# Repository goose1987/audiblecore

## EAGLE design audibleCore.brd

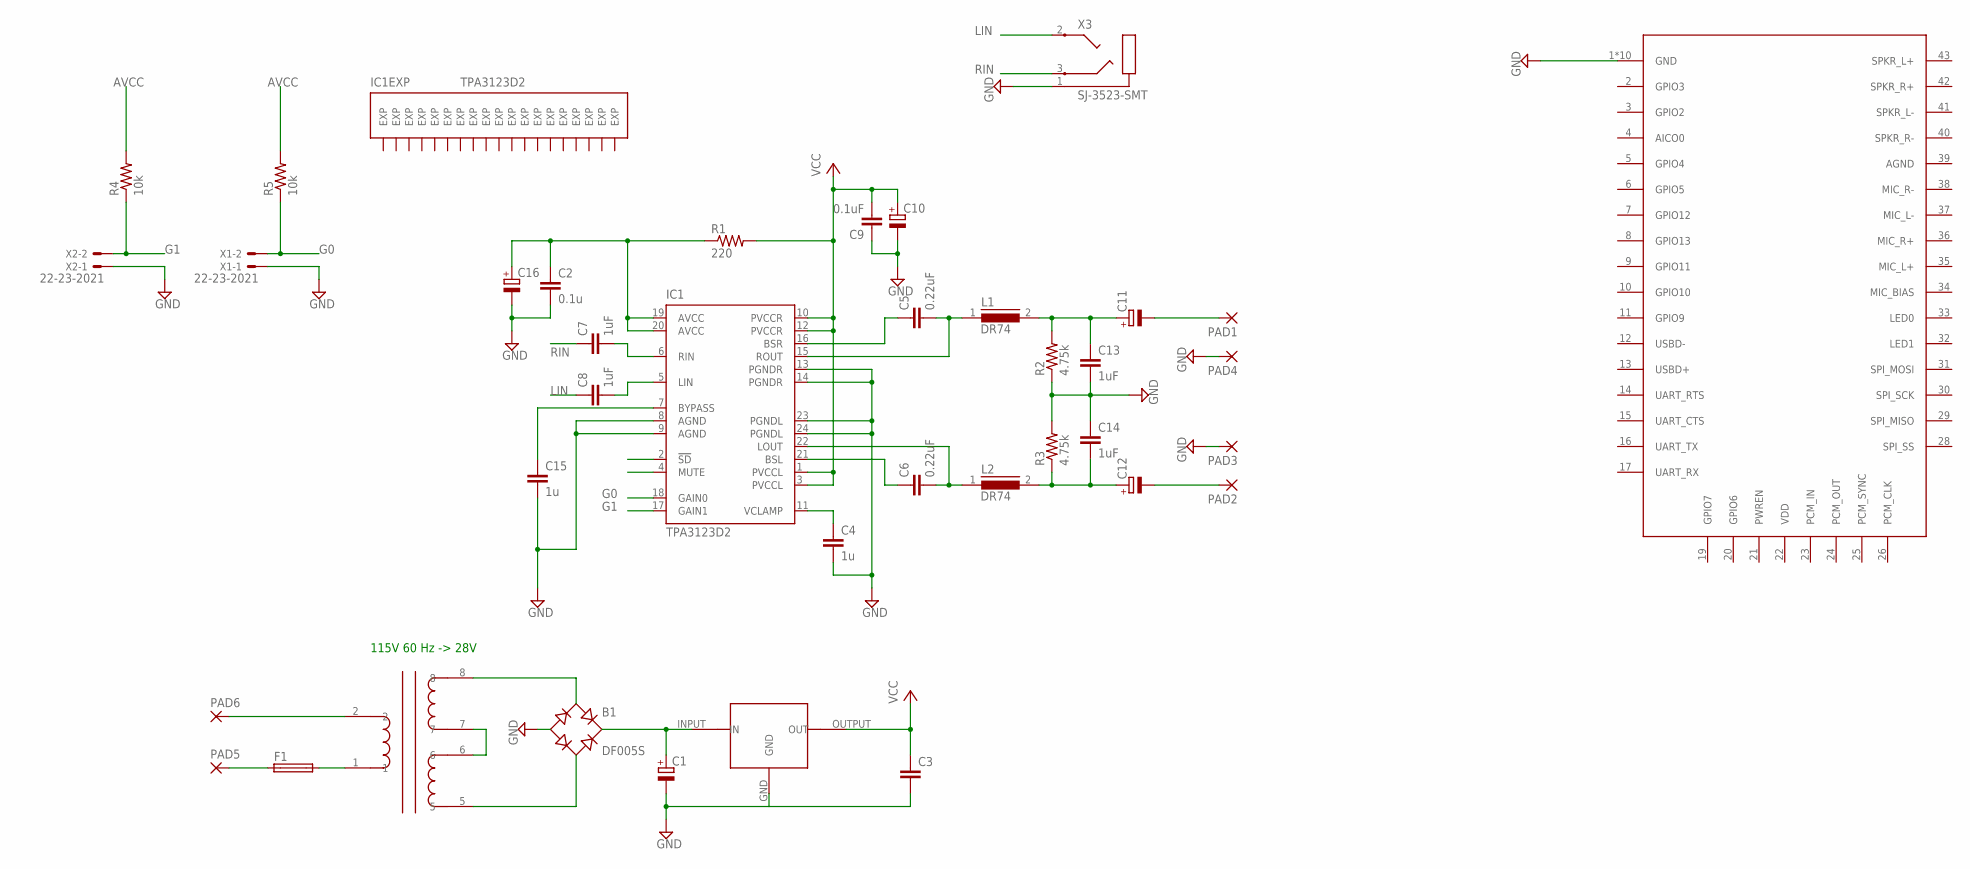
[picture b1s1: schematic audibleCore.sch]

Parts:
B1: DF005S; DFS
C1, C10, C11, C12, C16: CPOL-EUG; PANASONIC_G
C2: 0.1u; C1206
C3: C-EUC1206; C1206
C4, C15: 1u; C1206
C5, C6: 0.22uF; C1206
C7, C8, C13, C14: 1uF; C1206
C9: 0.1uF; C1206
F1: GSH15
IC1: TPA3123D2; PWP-TSSOP24
L1, L2: DR74
PAD1, PAD2, PAD3, PAD4, PAD5, PAD6: SMD5; SMD2,54-5,08
R1: 220; R1206
R2, R3: 4.75k; R1206
R4, R5: 10k; R1206
U$1: ST-7-24; ST-7
U$2: L78XX; D2PAK
U$3: RN-52
X1, X2: 22-23-2021
X3: SJ-3523-SMT

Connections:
AVCC: C2.1, C16.+, IC1.19 (AVCC), IC1.20 (AVCC), R1.1, R4.2, R5.2
G0: IC1.18 (GAIN0), R5.1, X1.2
G1: IC1.17 (GAIN1), R4.1, X2.2
GND: B1.-, C1.-, C2.2, C3.2, C4.2, C9.1, C10.-, C13.2, C14.1, C15.2, C16.-, IC1.8 (AGND), IC1.9 (AGND), IC1.13 (PGNDR), IC1.14 (PGNDR), IC1.23 (PGNDL), IC1.24 (PGNDL), PAD3.1, PAD4.1, R2.1, R3.2, U$2.GND, U$3.1 (GND), U$3.18 (GND), U$3.27 (GND), U$3.44 (GND), U$3.45 (GND), U$3.46 (GND), U$3.47 (GND), U$3.48 (GND), U$3.49 (GND), U$3.50 (GND), X1.1, X2.1, X3.1 (EARTH)
LIN: C8.1, X3.2 (TIP)
unnamed: U$1.6, U$1.7
unnamed: B1.AC1, U$1.8
unnamed: B1.AC2, U$1.5
unnamed: B1.+, C1.+, U$2.INPUT (IN)
unnamed: C12.-, PAD2.1
unnamed: C4.1, IC1.11 (VCLAMP)
unnamed: C5.1, IC1.16 (BSR)
unnamed: C6.1, IC1.21 (BSL)
unnamed: C6.2, IC1.22 (LOUT), L2.1
unnamed: C5.2, IC1.15 (ROUT), L1.1
unnamed: C15.1, IC1.7 (BYPASS)
unnamed: C7.2, IC1.6 (RIN)
unnamed: C8.2, IC1.5 (LIN)
unnamed: C11.+, C13.1, L1.2, R2.2
unnamed: C12.+, C14.2, L2.2, R3.1
unnamed: C11.-, PAD1.1
unnamed: PAD6.1, U$1.2
unnamed: F1.2, U$1.1
unnamed: F1.1, PAD5.1
RIN: C7.1, X3.3 (RING)
VCC: C3.1, C9.2, C10.+, IC1.1 (PVCCL), IC1.3 (PVCCL), IC1.10 (PVCCR), IC1.12 (PVCCR), R1.2, U$2.OUTPUT (OUT)

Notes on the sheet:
115V 60 Hz -> 28V

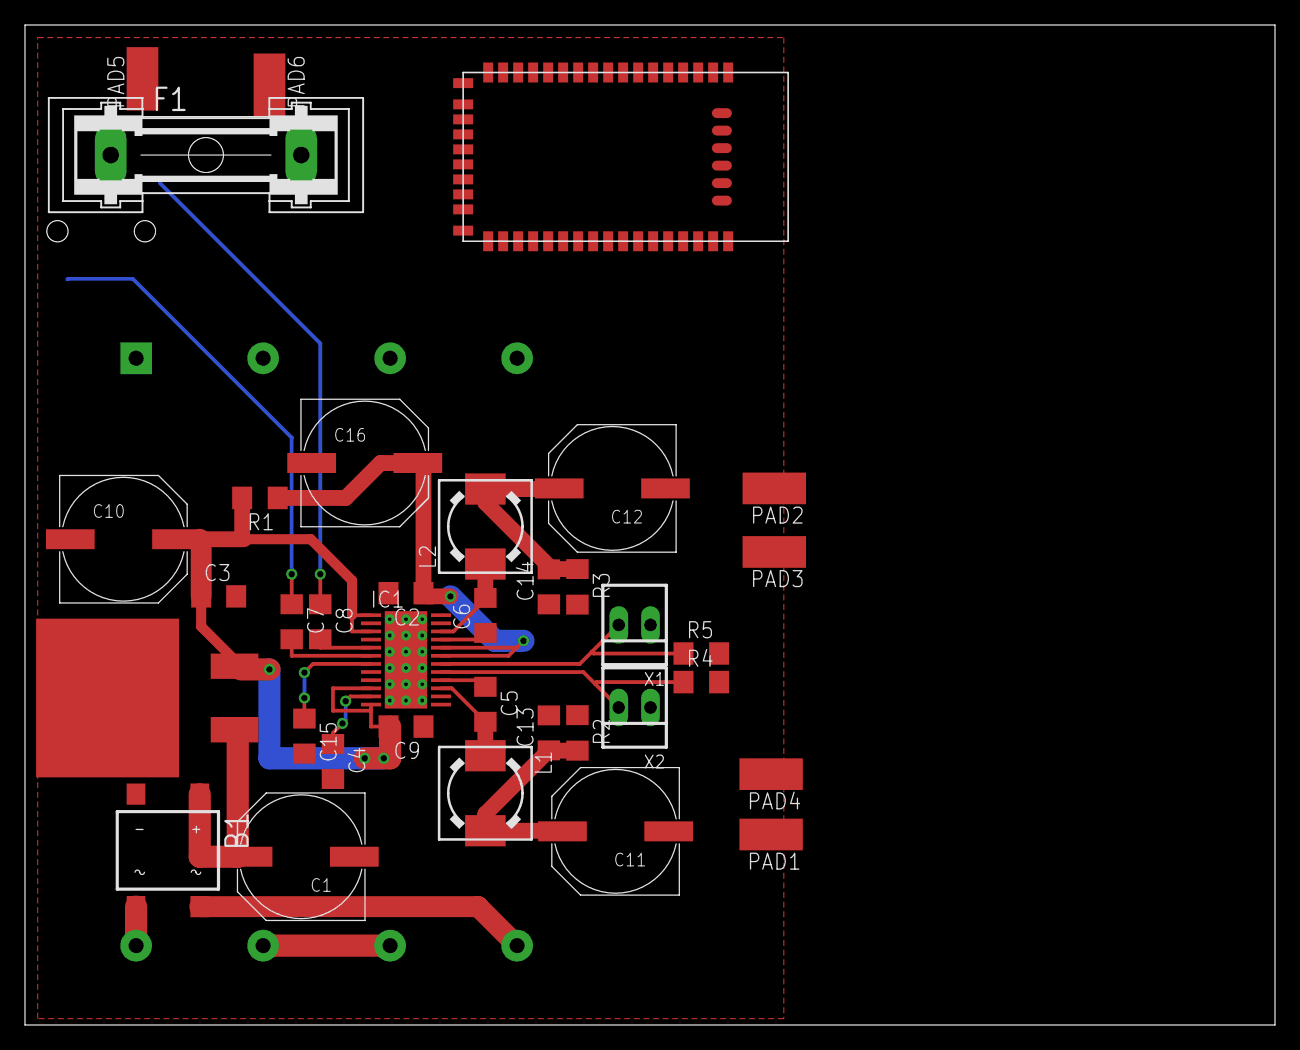
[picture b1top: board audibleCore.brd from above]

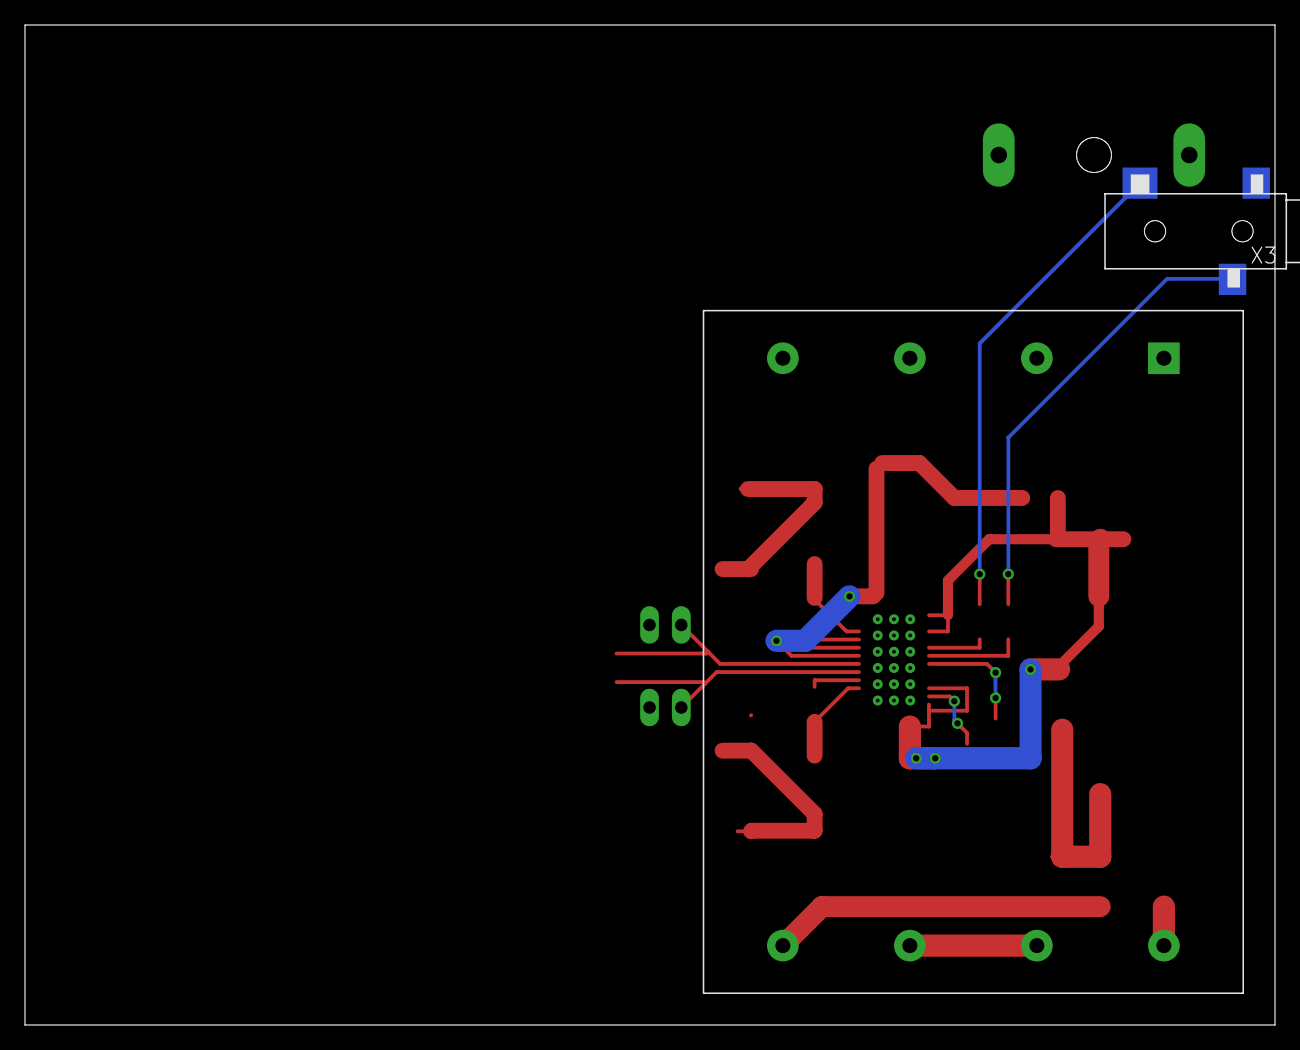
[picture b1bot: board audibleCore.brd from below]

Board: 2 copper layers, 100.0 x 80.0 mm, 38 parts (2 on the bottom side), 26 nets.

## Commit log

2013-09-07 9/7/2013 initial commit
